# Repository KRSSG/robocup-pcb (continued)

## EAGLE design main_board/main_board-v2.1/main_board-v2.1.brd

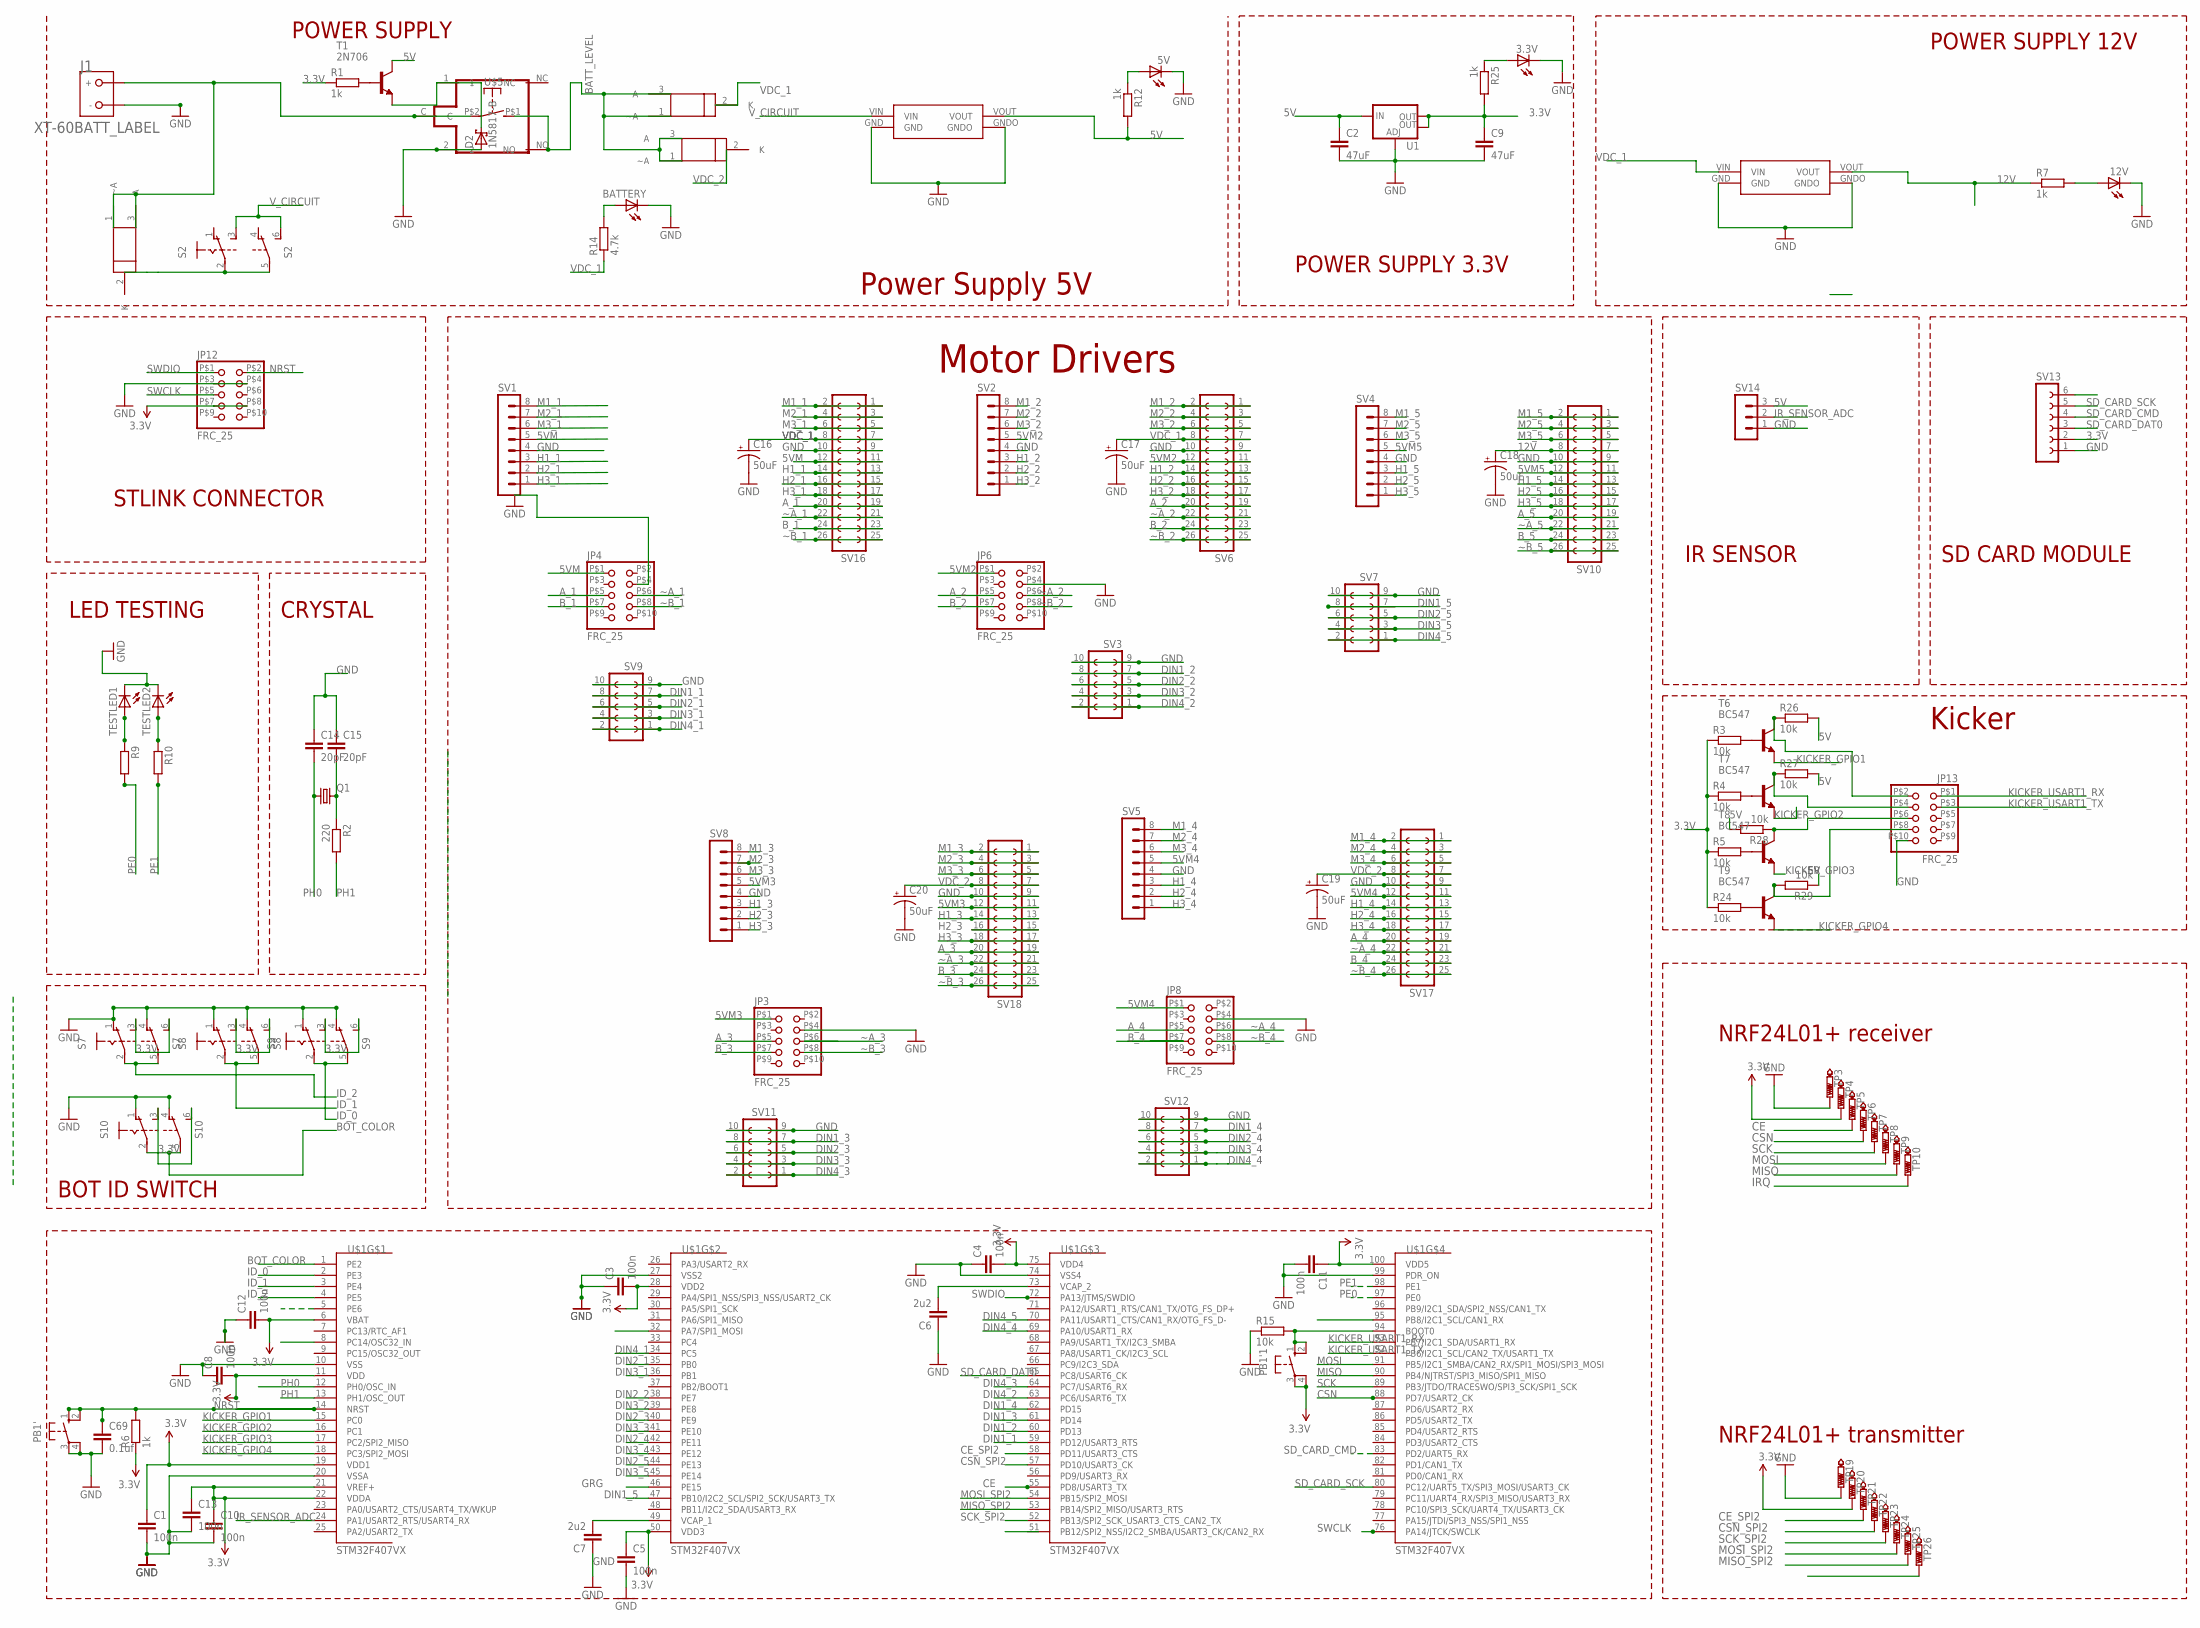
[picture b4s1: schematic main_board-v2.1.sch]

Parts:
3.3V, 5V, 12V: LEDCHIPLED_1206; CHIPLED_1206
BATTERY: LEDCHIPLED_1206; CHIPLED_1206
C1, C3, C4, C5, C8, C10, C11, C12, C13: 100n; C1206
C2, C9: 47uF; C1206
C6, C7: 2u2; C1206
C14, C15: 20pF; C1206
C16, C17, C18, C19, C20: 50uF; E3,5-8
C69: 0.1uf; C1206
D2: 1N5817-B; DO41-7.6
J1: XT-60BATT_LABEL; XT-60
JP3, JP4, JP6, JP8, JP12, JP13: FRC_25; FRC2*5
PB1', PB1'1: 10-XX; B3F-10XX
Q1: CRYSTALHC49U-V; HC49U-V
R1, R6, R7, R12, R25: 1k; R1206
R2: 220; R1206
R3, R4, R5, R15, R24, R26, R27, R28, R29: 10k; R1206
R9, R10: R-EU_R1206; R1206
R14: 4.7k; R1206
S2, S7, S8, S9, S10: A68-A31
SV1, SV2, SV4, SV5, SV8: MA08-1
SV3, SV7, SV9, SV11, SV12: FE05-2
SV6, SV10, SV16, SV17, SV18: FE13-2
SV13: FE06-1; FE06
SV14: MA03-1
T1: 2N706; TO18
T6, T7, T8, T9: BC547; TO92
TESTLED1, TESTLED2: LEDCHIPLED_1206; CHIPLED_1206
TP3, TP4, TP5, TP6, TP7, TP8, TP9, TP10, TP19, TP20, TP21, TP22, TP23, TP24, TP25, TP26: PTR1PAD1-13; P1-13
U1: V_REG_LM1117SOT223; SOT223
U2, U3, U4: LP38690DT-3.3; TO228P1042X238-3N
U$1: STM32F407VX; LQFP100
U$2: REL
U$3, U$4: BUCK
U$5: SWITCH_DA10; DA10

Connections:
3.3V: C1.1, C3.2, C4.2, C5.1, C8.2, C9.1, C10.1, C11.1, C12.2, C13.1, JP12.P$7 (7), JP12.P$8 (8), PB1'1.3, PB1'1.4 (P1), R3.1, R4.1, R5.1, R6.1, R24.1, R25.2, S7.3 (S), S7.6 (S), S8.3 (S), S8.6 (S), S9.3 (S), S9.6 (S), S10.3 (S), S10.6 (S), SV13.2, TP4.TP, TP20.TP, U1.2 (OUT), U1.4 (OUT), U$1.6 (VBAT), U$1.11 (VDD), U$1.19 (VDD1), U$1.21 (VREF+), U$1.22 (VDDA), U$1.28 (VDD2), U$1.50 (VDD3), U$1.75 (VDD4), U$1.100 (VDD5)
5V: C2.1, R12.2, R26.2, R27.2, R28.2, R29.1, SV14.3, T1.3 (C), U1.3 (IN), U$3.VOUT
5VM: JP4.P$1 (1), SV1.5, SV16.11, SV16.12
5VM2: JP6.P$1 (1), SV2.5, SV6.11, SV6.12
5VM3: JP3.P$1 (1), SV8.5, SV18.11, SV18.12
5VM4: JP8.P$1 (1), SV5.5, SV17.11, SV17.12
5VM5: SV4.5, SV10.11, SV10.12
12V: C18.+, R7.1, SV10.7, SV10.8, U$4.VOUT
A_1: JP4.P$5 (5), SV16.19, SV16.20
A_2: JP6.P$5 (5), SV6.19, SV6.20
A_3: JP3.P$5 (5), SV18.19, SV18.20
A_4: JP8.P$5 (5), SV17.19, SV17.20
A_5: SV10.19, SV10.20
BATT_LEVEL: U2.1 (~A), U2.3 (A), U4.1 (~A), U4.3 (A), U$2.NO, U$5.P$1 (S)
BOT_COLOR: S10.2, S10.5, U$1.1 (PE2)
B_1: JP4.P$7 (7), SV16.23, SV16.24
B_2: JP6.P$7 (7), SV6.23, SV6.24
B_3: JP3.P$7 (7), SV18.23, SV18.24
B_4: JP8.P$7 (7), SV17.23, SV17.24
B_5: SV10.23, SV10.24
CE: TP5.TP, U$1.55 (PD8/USART3_TX)
CE_SPI2: TP21.TP, U$1.58 (PD11/USART3_CTS)
CSN: TP6.TP, U$1.88 (PD7/USART2_CK)
CSN_SPI2: TP22.TP, U$1.57 (PD10/USART3_CK)
DIN1_1: SV9.7, SV9.8, U$1.59 (PD12/USART3_RTS)
DIN1_2: SV3.7, SV3.8, U$1.60 (PD13)
DIN1_3: SV11.7, SV11.8, U$1.61 (PD14)
DIN1_4: SV12.7, SV12.8, U$1.62 (PD15)
DIN1_5: SV7.7, SV7.8, U$1.47 (PB10/I2C2_SCL/SPI2_SCK/USART3_TX)
DIN2_1: SV9.5, SV9.6, U$1.35 (PB0)
DIN2_2: SV3.5, SV3.6, U$1.38 (PE7)
DIN2_3: SV11.5, SV11.6, U$1.40 (PE9)
DIN2_4: SV12.5, SV12.6, U$1.42 (PE11)
DIN2_5: SV7.5, SV7.6, U$1.44 (PE13)
DIN3_1: SV9.3, SV9.4, U$1.36 (PB1)
DIN3_2: SV3.3, SV3.4, U$1.39 (PE8)
DIN3_3: SV11.3, SV11.4, U$1.41 (PE10)
DIN3_4: SV12.3, SV12.4, U$1.43 (PE12)
DIN3_5: SV7.3, SV7.4, U$1.45 (PE14)
DIN4_1: SV9.1, SV9.2, U$1.34 (PC5)
DIN4_2: SV3.1, SV3.2, U$1.63 (PC6/USART6_TX)
DIN4_3: SV11.1, SV11.2, U$1.64 (PC7/USART6_RX)
DIN4_4: SV12.1, SV12.2, U$1.69 (PA10/USART1_RX)
DIN4_5: SV7.1, SV7.2, U$1.70 (PA11/USART1_CTS/CAN1_RX/OTG_FS_D-)
GND: 3.3V.C, 5V.C, 12V.C, BATTERY.C, C1.2, C2.2, C3.1, C4.1, C5.2, C6.1, C7.1, C8.1, C9.2, C10.2, C11.2, C12.1, C13.2, C14.1, C15.1, C16.-, C17.-, C18.-, C19.-, C20.-, C69.2, D2.A, J1.GND (-), JP3.P$4 (4), JP4.P$4 (4), JP6.P$4 (4), JP8.P$4 (4), JP12.P$3 (3), JP12.P$4 (4), JP13.P$10 (10), PB1'.3, PB1'.4 (P1), R15.1, S7.1 (O), S7.4 (O), S8.1 (O), S8.4 (O), S9.1 (O), S9.4 (O), S10.1 (O), S10.4 (O), SV1.4, SV2.4, SV3.9, SV3.10, SV4.4, SV5.4, SV6.9, SV6.10, SV7.9, SV7.10, SV8.4, SV9.9, SV9.10, SV10.9, SV10.10, SV11.9, SV11.10, SV12.9, SV12.10, SV13.1, SV14.1, SV16.9, SV16.10, SV17.9, SV17.10, SV18.9, SV18.10, TESTLED1.C, TESTLED2.C, TP3.TP, TP19.TP, U1.1 (ADJ), U$1.10 (VSS), U$1.20 (VSSA), U$1.27 (VSS2), U$1.74 (VSS4), U$1.99 (PDR_ON), U$2.2, U$3.GND, U$3.GNDO, U$4.GND, U$4.GNDO
GRG: U$1.46 (PE15)
H1_1: SV1.3, SV16.13, SV16.14
H1_2: SV2.3, SV6.13, SV6.14
H1_3: SV8.3, SV18.13, SV18.14
H1_4: SV5.3, SV17.13, SV17.14
H1_5: SV4.3, SV10.13, SV10.14
H2_1: SV1.2, SV16.15, SV16.16
H2_2: SV2.2, SV6.15, SV6.16
H2_3: SV8.2, SV18.15, SV18.16
H2_4: SV5.2, SV17.15, SV17.16
H2_5: SV4.2, SV10.15, SV10.16
H3_1: SV1.1, SV16.17, SV16.18
H3_2: SV2.1, SV6.17, SV6.18
H3_3: SV8.1, SV18.17, SV18.18
H3_4: SV5.1, SV17.17, SV17.18
H3_5: SV4.1, SV10.17, SV10.18
ID_0: S9.2, S9.5, U$1.2 (PE3)
ID_1: S8.2, S8.5, U$1.3 (PE4)
ID_2: S7.2, S7.5, U$1.4 (PE5)
IRQ: TP10.TP
IRQ_SPI2: U$1.8 (PC14/OSC32_IN)
IR_SENSOR_ADC: SV14.2, U$1.24 (PA1/USART2_RTS/USART4_RX)
KICKER_GPIO1: T6.1 (E), U$1.15 (PC0)
KICKER_GPIO2: T7.1 (E), U$1.16 (PC1)
KICKER_GPIO3: T8.1 (E), U$1.17 (PC2/SPI2_MISO)
KICKER_GPIO4: T9.1 (E), U$1.18 (PC3/SPI2_MOSI)
KICKER_USART1_RX: JP13.P$1 (1), U$1.93 (PB7/I2C1_SDA/USART1_RX)
KICKER_USART1_TX: JP13.P$3 (3), U$1.92 (PB6/I2C1_SCL/CAN2_TX/USART1_TX)
M1_1: SV1.8, SV16.1, SV16.2
M1_2: SV2.8, SV6.1, SV6.2
M1_3: SV8.8, SV18.1, SV18.2
M1_4: SV5.8, SV17.1, SV17.2
M1_5: SV4.8, SV10.1, SV10.2
M2_1: SV1.7, SV16.3, SV16.4
M2_2: SV2.7, SV6.3, SV6.4
M2_3: SV8.7, SV18.3, SV18.4
M2_4: SV5.7, SV17.3, SV17.4
M2_5: SV4.7, SV10.3, SV10.4
M3_1: SV1.6, SV16.5, SV16.6
M3_2: SV2.6, SV6.5, SV6.6
M3_3: SV8.6, SV18.5, SV18.6
M3_4: SV5.6, SV17.5, SV17.6
M3_5: SV4.6, SV10.5, SV10.6
MISO: TP9.TP, U$1.90 (PB4/NJTRST/SPI3_MISO/SPI1_MISO)
MISO_SPI2: TP25.TP, U$1.53 (PB14/SPI2_MISO/USART3_RTS)
MOSI: TP8.TP, U$1.91 (PB5/I2C1_SMBA/CAN2_RX/SPI1_MOSI/SPI3_MO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)
MOSI_SPI2: TP24.TP, U$1.54 (PB15/SPI2_MOSI)
unnamed: R10.1, TESTLED2.A
unnamed: C7.2, U$1.49 (VCAP_1)
unnamed: C6.2, U$1.73 (VCAP_2)
unnamed: PB1'1.1 (S), PB1'1.2 (S1), R15.2, U$1.94 (BOOT0)
unnamed: R9.1, TESTLED1.A
unnamed: C15.2, Q1.2, R2.1
unnamed: 5V.A, R12.1
unnamed: J1.BATT (+), U3.1 (~A), U3.3 (A), U$2.C, U$5.P$2
unnamed: 12V.A, R7.2
unnamed: BATTERY.A, R14.2
unnamed: 3.3V.A, R25.1
unnamed: R1.2, T1.2 (B)
unnamed: D2.C, T1.1 (E), U$2.1
unnamed: S2.2, S2.5, U3.2 (K)
unnamed: R5.2, T8.2 (B)
unnamed: R3.2, T6.2 (B)
unnamed: R4.2, T7.2 (B)
unnamed: R24.2, T9.2 (B)
unnamed: JP13.P$2 (2), R26.1, T6.3 (C)
unnamed: JP13.P$4 (4), R27.1, T7.3 (C)
unnamed: JP13.P$6 (6), R28.1, T8.3 (C)
unnamed: JP13.P$8 (8), R29.2, T9.3 (C)
NRST: C69.1, JP12.P$2 (2), PB1'.1 (S), PB1'.2 (S1), R6.2, U$1.14 (NRST)
PE0: R9.2, U$1.97 (PE0)
PE1: R10.2, U$1.98 (PE1)
PH0: C14.2, Q1.1, U$1.12 (PH0/OSC_IN)
PH1: R2.2, U$1.13 (PH1/OSC_OUT)
SCK: TP7.TP, U$1.89 (PB3/JTDO/TRACESWO/SPI3_SCK/SPI1_SCK)
SCK_SPI2: TP23.TP, U$1.52 (PB13/SPI2_SCK_USART3_CTS_CAN2_TX)
SD_CARD_CMD: SV13.4, U$1.83 (PD2/UART5_RX)
SD_CARD_DAT0: SV13.3, U$1.65 (PC8/USART6_CK)
SD_CARD_SCK: SV13.5, U$1.80 (PC12/UART5_TX/SPI3_MOSI/USART3_CK)
SWCLK: JP12.P$5 (5), U$1.76 (PA14/JTCK/SWCLK)
SWDIO: JP12.P$1 (1), U$1.72 (PA13/JTMS/SWDIO)
VDC_1: C16.+, C17.+, R14.1, SV6.7, SV6.8, SV16.7, SV16.8, U4.2 (K), U$4.VIN
VDC_2: C19.+, C20.+, SV17.7, SV17.8, SV18.7, SV18.8, U2.2 (K)
V_CIRCUIT: S2.3 (S), S2.6 (S), U$3.VIN
~A_1: JP4.P$6 (6), SV16.21, SV16.22
~A_2: JP6.P$6 (6), SV6.21, SV6.22
~A_3: JP3.P$6 (6), SV18.21, SV18.22
~A_4: JP8.P$6 (6), SV17.21, SV17.22
~A_5: SV10.21, SV10.22
~B_1: JP4.P$8 (8), SV16.25, SV16.26
~B_2: JP6.P$8 (8), SV6.25, SV6.26
~B_3: JP3.P$8 (8), SV18.25, SV18.26
~B_4: JP8.P$8 (8), SV17.25, SV17.26
~B_5: SV10.25, SV10.26

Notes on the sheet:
NRF24L01+ receiver
STLINK CONNECTOR
LED TESTING
Motor Drivers
POWER SUPPLY 12V
POWER SUPPLY 3.3V
Kicker
NRF24L01+ transmitter
POWER SUPPLY
Power Supply 5V
BOT ID SWITCH
CRYSTAL
SD CARD MODULE
IR SENSOR

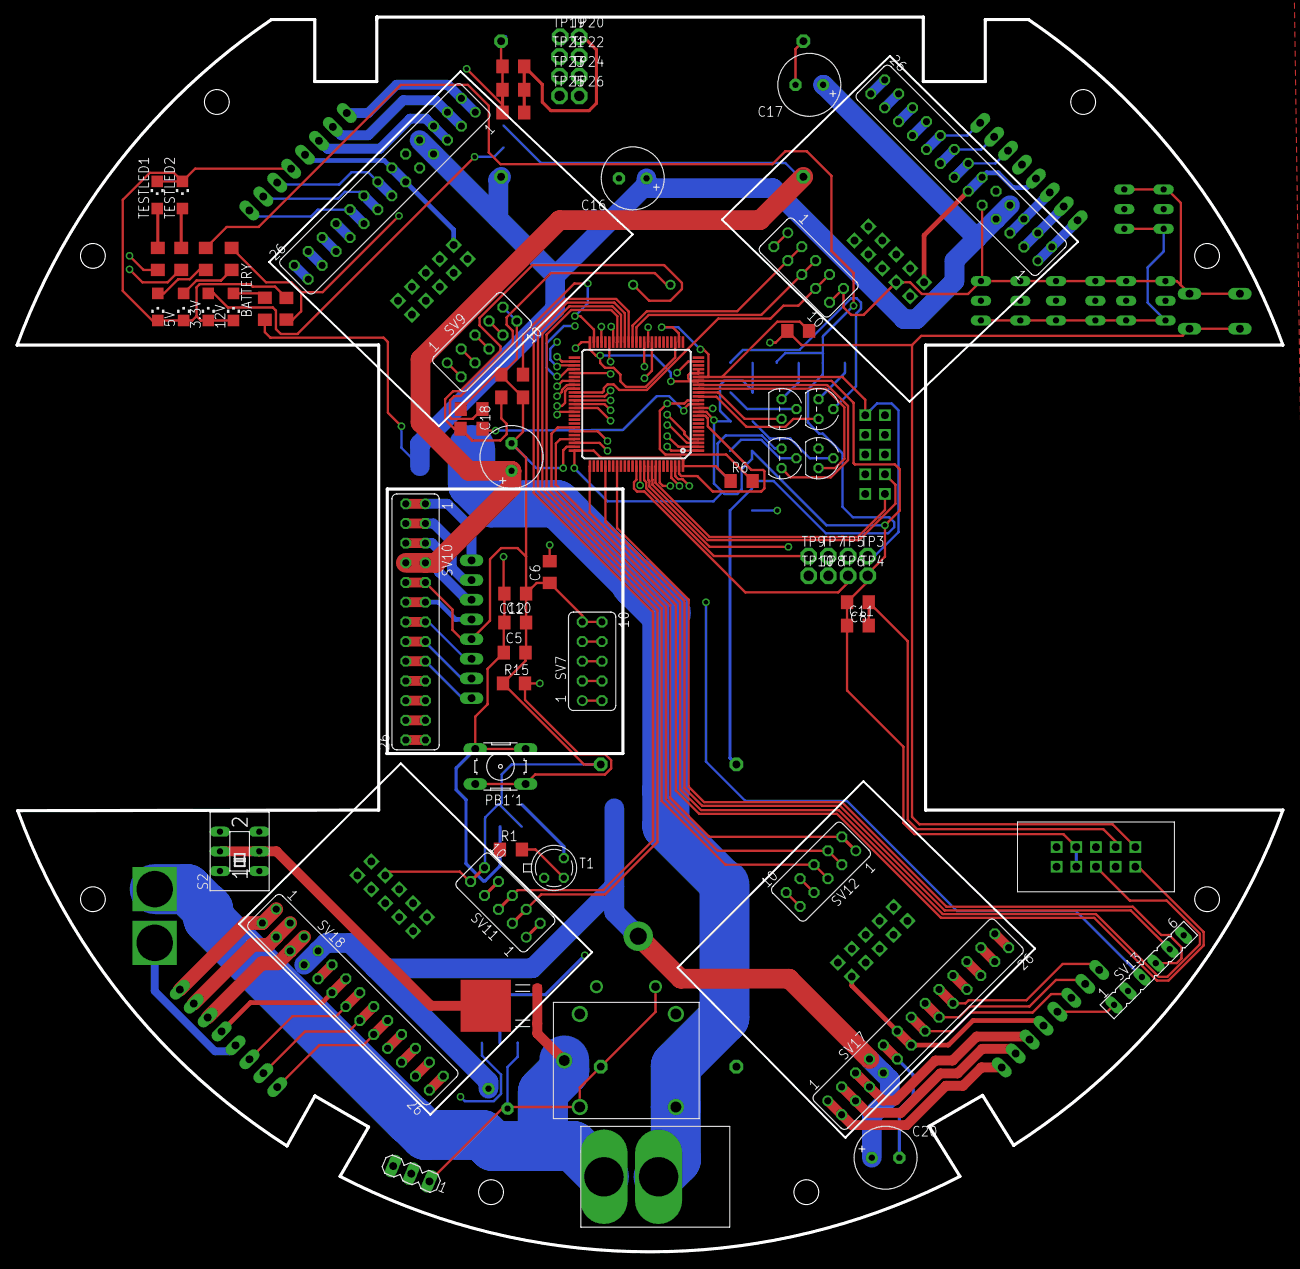
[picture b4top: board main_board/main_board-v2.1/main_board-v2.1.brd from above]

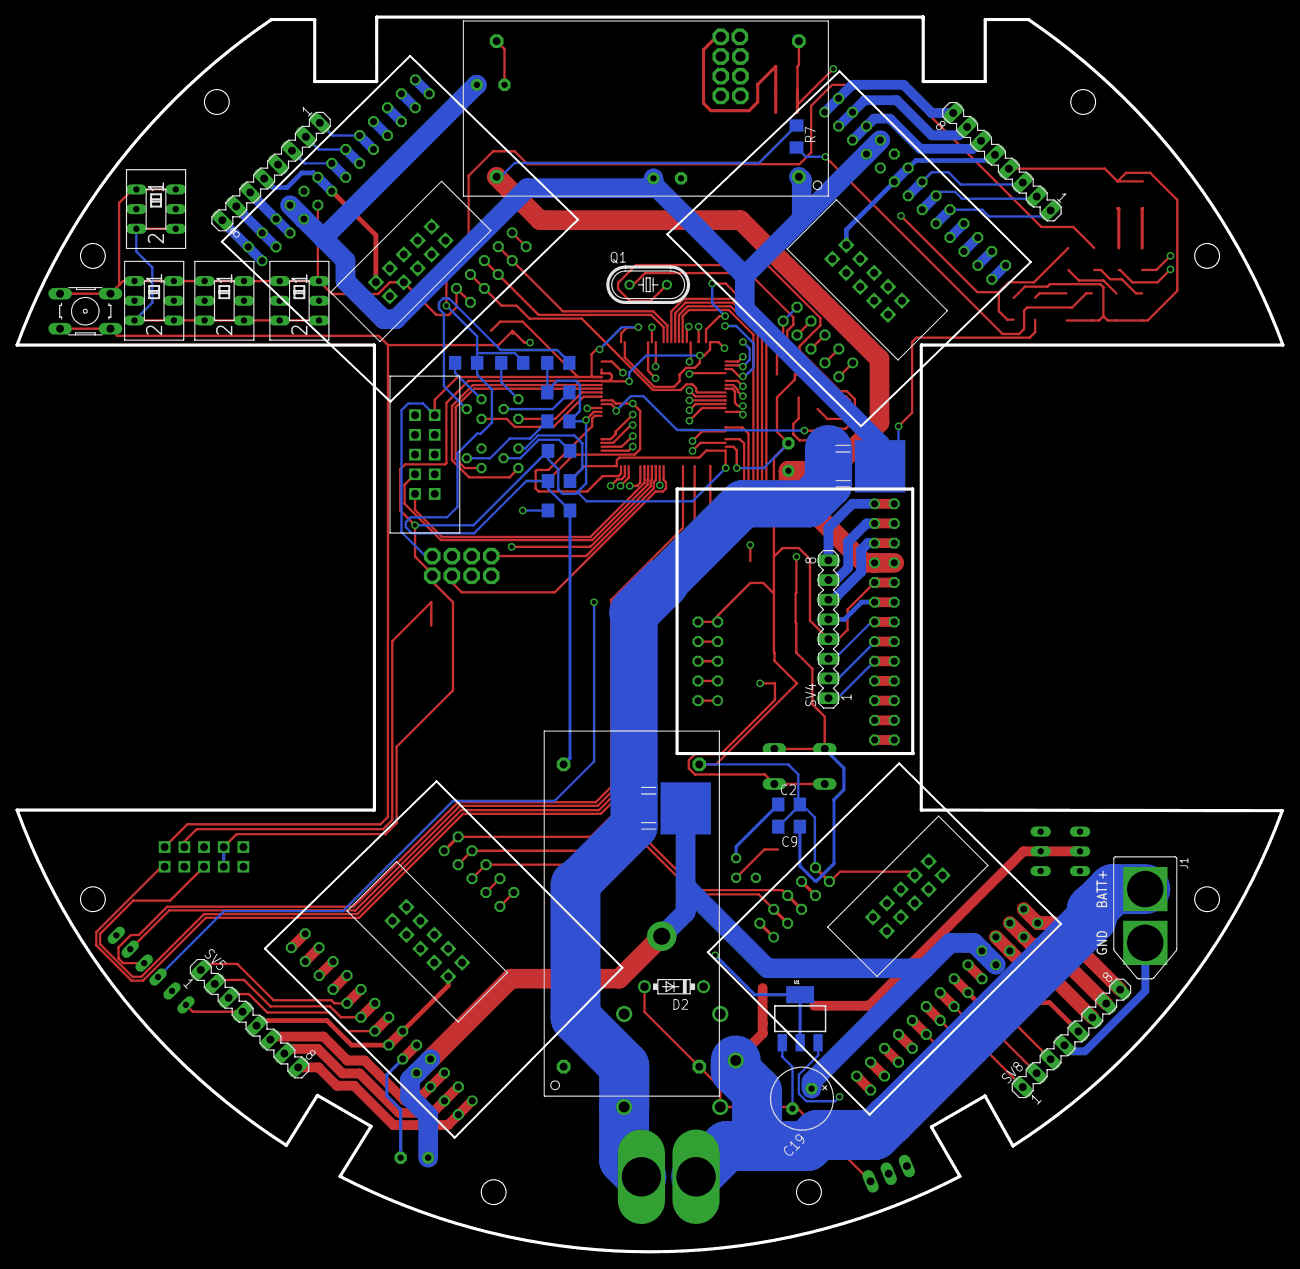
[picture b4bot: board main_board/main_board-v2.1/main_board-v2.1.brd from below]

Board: 4 copper layers, 163.3 x 159.3 mm, 108 parts (35 on the bottom side), 136 nets.

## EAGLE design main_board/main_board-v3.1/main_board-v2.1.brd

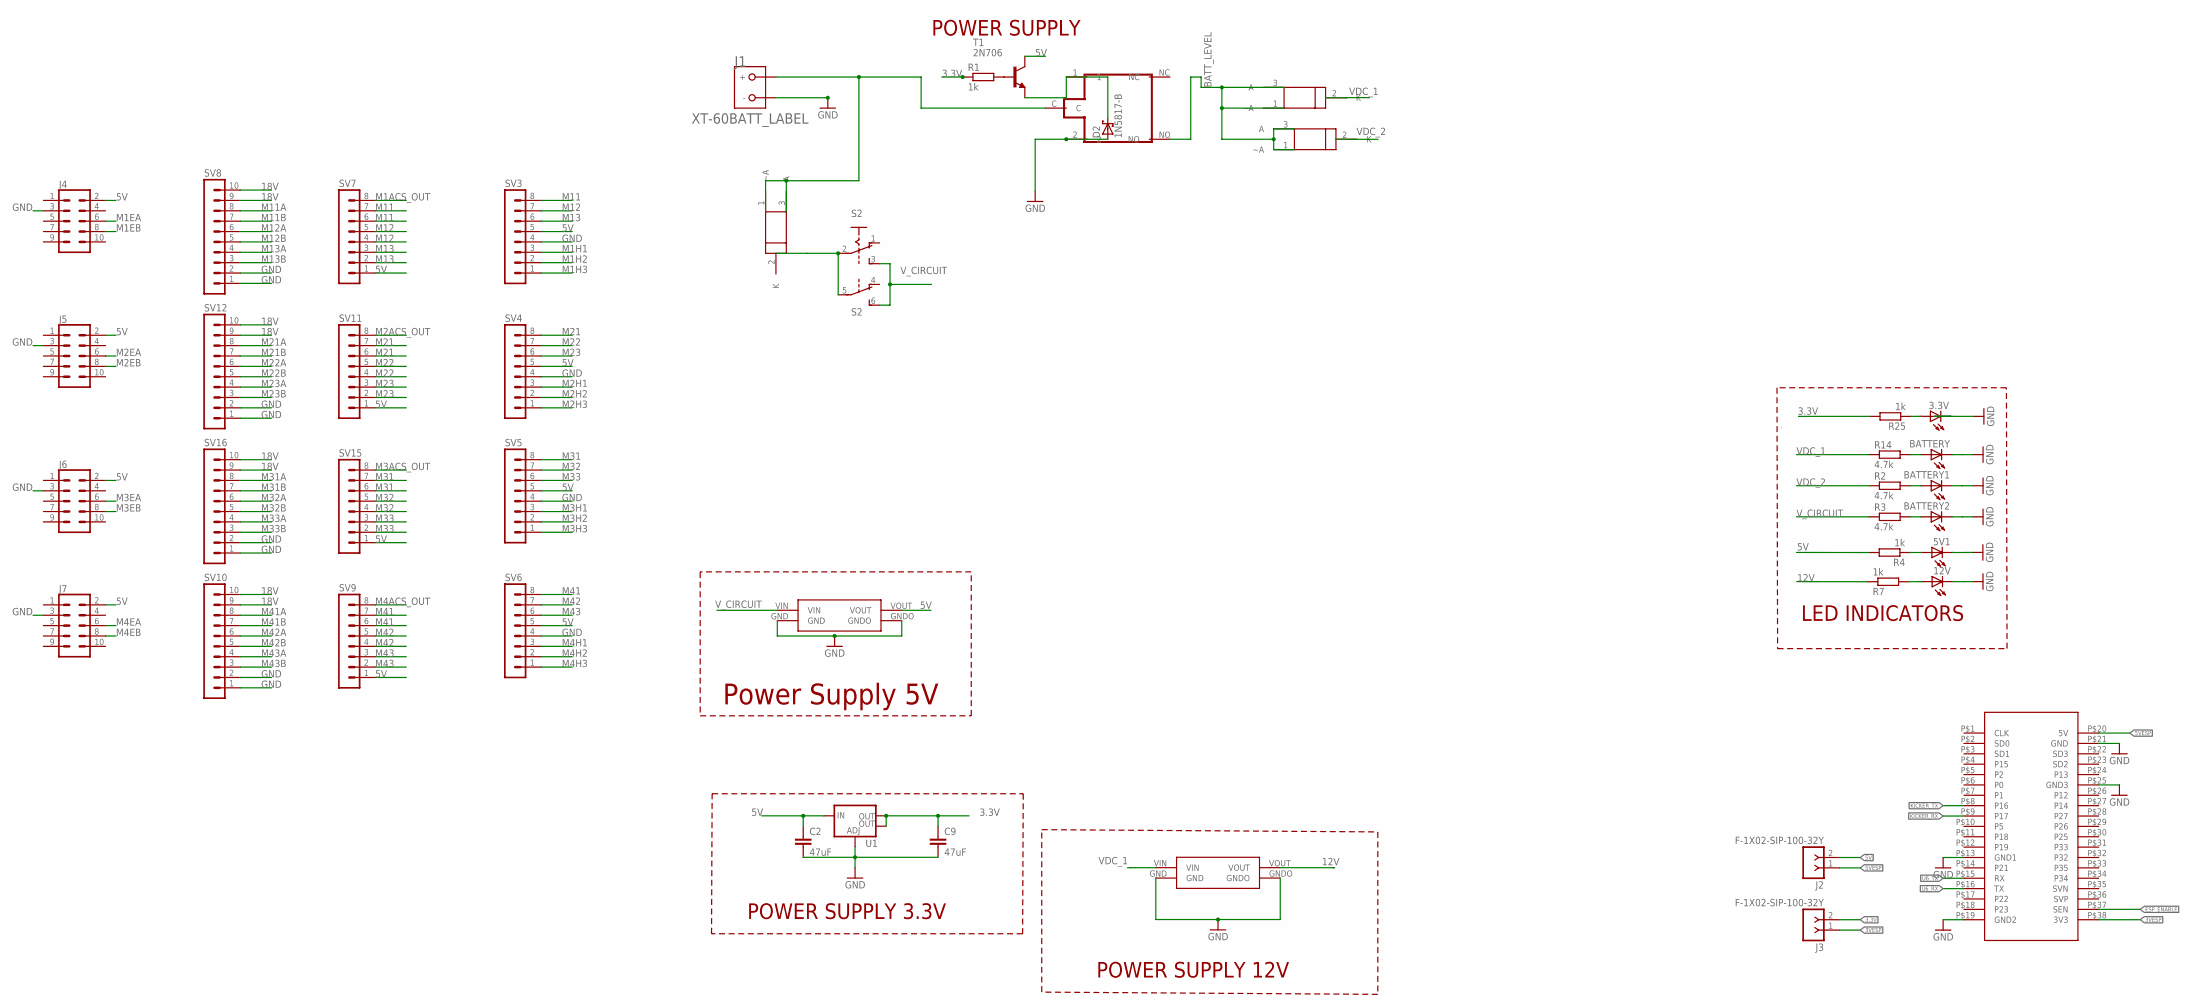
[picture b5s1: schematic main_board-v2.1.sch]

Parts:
3.3V, 5V1, 12V: LEDCHIPLED_0805; CHIPLED_0805
BATTERY, BATTERY1, BATTERY2: LEDCHIPLED_0805; CHIPLED_0805
C2, C9: 47uF; C1206
D2: 1N5817-B; DO41-7.6
J1: XT-60BATT_LABEL; XT-60
J2, J3: F-1X02-SIP-100-32Y; SIP-100-02-32Y
J4, J5, J6, J7: CONN_05X2SHD_LOCK; 2X5-SHROUDED_LOCK
R1, R4, R7, R25: 1k; R1206
R2, R3, R14: 4.7k; R1206
S2: A68-A31
SV3, SV4, SV5, SV6, SV7, SV9, SV11, SV15: MA08-1
SV8, SV10, SV12, SV16: MA10-1
T1: 2N706; TO18
U1: V_REG_LM1117SOT223; SOT223
U2, U3, U4: LP38690DT-3.3; TO228P1042X238-3N
U$2: REL
U$3, U$4: BUCK
U$6: NODEMCU32S; NODEMCU32

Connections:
3.3V: C9.1, J3.2, R1.1, R25.2, U1.2 (OUT), U1.4 (OUT)
3VESP: J3.1, U$6.P$38 (3V3)
5V: C2.1, J2.2, J4.2, J5.2, J6.2, J7.2, R4.2, SV3.5, SV4.5, SV5.5, SV6.5, SV7.1, SV9.1, SV11.1, SV15.1, T1.3 (C), U1.3 (IN), U$3.VOUT
5VESP: J2.1, U$6.P$20 (5V)
12V: R7.1, U$4.VOUT
18V: SV8.9, SV8.10, SV10.9, SV10.10, SV12.9, SV12.10, SV16.9, SV16.10
BATT_LEVEL: U2.1 (~A), U2.3 (A), U4.1 (~A), U4.3 (A), U$2.NO
ESP_ENABLE: U$6.P$37 (SEN)
GND: 3.3V.C, 5V1.C, 12V.C, BATTERY.C, BATTERY1.C, BATTERY2.C, C2.2, C9.2, D2.A, J1.GND (-), J4.3, J5.3, J6.3, J7.3, SV3.4, SV4.4, SV5.4, SV6.4, SV8.1, SV8.2, SV10.1, SV10.2, SV12.1, SV12.2, SV16.1, SV16.2, U1.1 (ADJ), U$2.2, U$3.GND, U$3.GNDO, U$4.GND, U$4.GNDO, U$6.P$13 (GND1), U$6.P$19 (GND2), U$6.P$21 (GND), U$6.P$25 (GND3)
INPUT: J1.BATT (+), U3.1 (~A), U3.3 (A), U$2.C
KICKER_RX: U$6.P$9 (P17)
KICKER_TX: U$6.P$8 (P16)
M1ACS_OUT: SV7.8
M1EA: J4.6
M1EB: J4.8
M1H1: SV3.3
M1H2: SV3.2
M1H3: SV3.1
M2ACS_OUT: SV11.8
M2EA: J5.6
M2EB: J5.8
M2H1: SV4.3
M2H2: SV4.2
M2H3: SV4.1
M3ACS_OUT: SV15.8
M3EA: J6.6
M3EB: J6.8
M3H1: SV5.3
M3H2: SV5.2
M3H3: SV5.1
M4ACS_OUT: SV9.8
M4EA: J7.6
M4EB: J7.8
M4H1: SV6.3
M4H2: SV6.2
M4H3: SV6.1
M11: SV3.8, SV7.6, SV7.7
M11A: SV8.8
M11B: SV8.7
M12: SV3.7, SV7.4, SV7.5
M12A: SV8.6
M12B: SV8.5
M13: SV3.6, SV7.2, SV7.3
M13A: SV8.4
M13B: SV8.3
M21: SV4.8, SV11.6, SV11.7
M21A: SV12.8
M21B: SV12.7
M22: SV4.7, SV11.4, SV11.5
M22A: SV12.6
M22B: SV12.5
M23: SV4.6, SV11.2, SV11.3
M23A: SV12.4
M23B: SV12.3
M31: SV5.8, SV15.6, SV15.7
M31A: SV16.8
M31B: SV16.7
M32: SV5.7, SV15.4, SV15.5
M32A: SV16.6
M32B: SV16.5
M33: SV5.6, SV15.2, SV15.3
M33A: SV16.4
M33B: SV16.3
M41: SV6.8, SV9.6, SV9.7
M41A: SV10.8
M41B: SV10.7
M42: SV6.7, SV9.4, SV9.5
M42A: SV10.6
M42B: SV10.5
M43: SV6.6, SV9.2, SV9.3
M43A: SV10.4
M43B: SV10.3
unnamed: BATTERY1.A, R2.2
unnamed: BATTERY2.A, R3.2
unnamed: 5V1.A, R4.1
unnamed: 12V.A, R7.2
unnamed: BATTERY.A, R14.2
unnamed: 3.3V.A, R25.1
unnamed: R1.2, T1.2 (B)
unnamed: D2.C, T1.1 (E), U$2.1
unnamed: S2.2, S2.5, U3.2 (K)
U6_RX: U$6.P$16 (TX)
U6_TX: U$6.P$15 (RX)
VDC_1: R14.1, U4.2 (K), U$4.VIN
VDC_2: R2.1, U2.2 (K)
V_CIRCUIT: R3.1, S2.3 (S), S2.6 (S), U$3.VIN

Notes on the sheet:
POWER SUPPLY
Power Supply 5V
POWER SUPPLY 12V
POWER SUPPLY 3.3V
LED INDICATORS

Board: 4 copper layers, 45 parts (0 on the bottom side), 33 nets, no tracks yet.

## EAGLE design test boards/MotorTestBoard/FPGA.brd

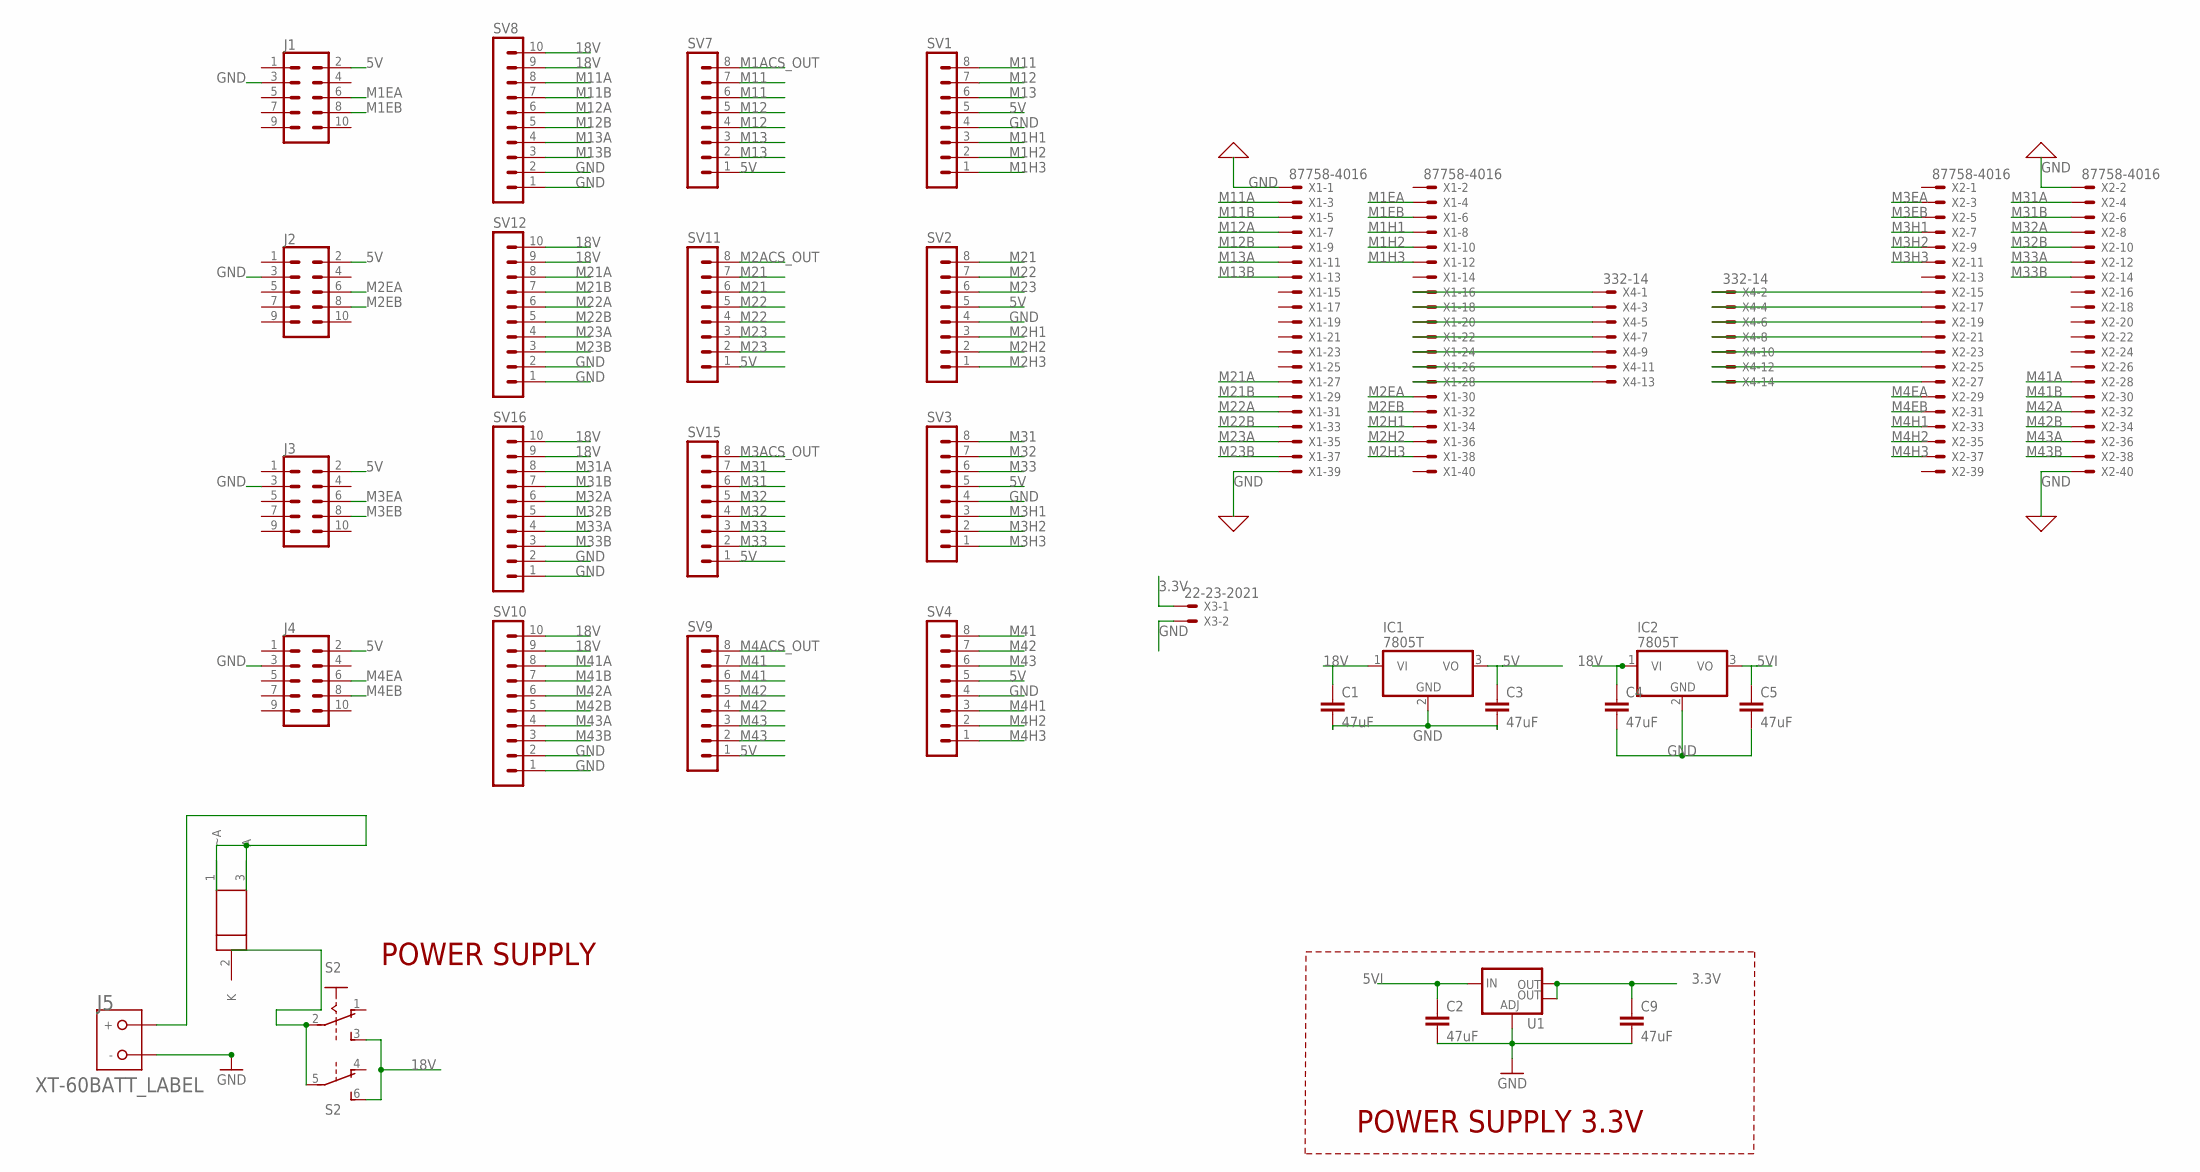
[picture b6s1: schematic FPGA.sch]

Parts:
C1, C2, C3, C4, C5, C9: 47uF; C1206
IC1, IC2: 7805T; TO220H
J1, J2, J3, J4: CONN_05X2SHD_LOCK; 2X5-SHROUDED_LOCK
J5: XT-60BATT_LABEL; XT-60
S2: A68-A31
SV1, SV2, SV3, SV4, SV7, SV9, SV11, SV15: MA08-1
SV8, SV10, SV12, SV16: MA10-1
U1: V_REG_LM1117SOT223; SOT223
U3: LP38690DT-3.3; TO228P1042X238-3N
X1, X2: 87758-4016
X3: 22-23-2021
X4: 332-14

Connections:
3.3V: C9.1, U1.2 (OUT), U1.4 (OUT), X3.1
5V: C3.1, IC1.3 (VO), J1.2, J2.2, J3.2, J4.2, SV1.5, SV2.5, SV3.5, SV4.5, SV7.1, SV9.1, SV11.1, SV15.1
5VI: C2.1, C5.1, IC2.3 (VO), U1.3 (IN)
18V: C1.1, C4.1, IC1.1 (VI), IC2.1 (VI), S2.3 (S), S2.6 (S), SV8.9, SV8.10, SV10.9, SV10.10, SV12.9, SV12.10, SV16.9, SV16.10
GND: C1.2, C2.2, C3.2, C4.2, C5.2, C9.2, IC1.2 (GND), IC2.2 (GND), J1.3, J2.3, J3.3, J4.3, J5.GND (-), SV1.4, SV2.4, SV3.4, SV4.4, SV8.1, SV8.2, SV10.1, SV10.2, SV12.1, SV12.2, SV16.1, SV16.2, U1.1 (ADJ), X1.1, X1.39, X2.2, X2.40, X3.2
INPUT: J5.BATT (+), U3.1 (~A), U3.3 (A)
M1ACS_OUT: SV7.8
M1EA: J1.6, X1.4
M1EB: J1.8, X1.6
M1H1: SV1.3, X1.8
M1H2: SV1.2, X1.10
M1H3: SV1.1, X1.12
M2ACS_OUT: SV11.8
M2EA: J2.6, X1.30
M2EB: J2.8, X1.32
M2H1: SV2.3, X1.34
M2H2: SV2.2, X1.36
M2H3: SV2.1, X1.38
M3ACS_OUT: SV15.8
M3EA: J3.6, X2.3
M3EB: J3.8, X2.5
M3H1: SV3.3, X2.7
M3H2: SV3.2, X2.9
M3H3: SV3.1, X2.11
M4ACS_OUT: SV9.8
M4EA: J4.6, X2.29
M4EB: J4.8, X2.31
M4H1: SV4.3, X2.33
M4H2: SV4.2, X2.35
M4H3: SV4.1, X2.37
M11: SV1.8, SV7.6, SV7.7
M11A: SV8.8, X1.3
M11B: SV8.7, X1.5
M12: SV1.7, SV7.4, SV7.5
M12A: SV8.6, X1.7
M12B: SV8.5, X1.9
M13: SV1.6, SV7.2, SV7.3
M13A: SV8.4, X1.11
M13B: SV8.3, X1.13
M21: SV2.8, SV11.6, SV11.7
M21A: SV12.8, X1.27
M21B: SV12.7, X1.29
M22: SV2.7, SV11.4, SV11.5
M22A: SV12.6, X1.31
M22B: SV12.5, X1.33
M23: SV2.6, SV11.2, SV11.3
M23A: SV12.4, X1.35
M23B: SV12.3, X1.37
M31: SV3.8, SV15.6, SV15.7
M31A: SV16.8, X2.4
M31B: SV16.7, X2.6
M32: SV3.7, SV15.4, SV15.5
M32A: SV16.6, X2.8
M32B: SV16.5, X2.10
M33: SV3.6, SV15.2, SV15.3
M33A: SV16.4, X2.12
M33B: SV16.3, X2.14
M41: SV4.8, SV9.6, SV9.7
M41A: SV10.8, X2.28
M41B: SV10.7, X2.30
M42: SV4.7, SV9.4, SV9.5
M42A: SV10.6, X2.32
M42B: SV10.5, X2.34
M43: SV4.6, SV9.2, SV9.3
M43A: SV10.4, X2.36
M43B: SV10.3, X2.38
unnamed: X1.16, X4.1
unnamed: X1.18, X4.3
unnamed: X1.20, X4.5
unnamed: X1.22, X4.7
unnamed: X1.24, X4.9
unnamed: X1.26, X4.11
unnamed: X1.28, X4.13
unnamed: X2.27, X4.14
unnamed: X2.25, X4.12
unnamed: X2.23, X4.10
unnamed: X2.21, X4.8
unnamed: X2.19, X4.6
unnamed: X2.17, X4.4
unnamed: X2.15, X4.2
unnamed: S2.2, S2.5, U3.2 (K)

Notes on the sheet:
POWER SUPPLY 3.3V
POWER SUPPLY

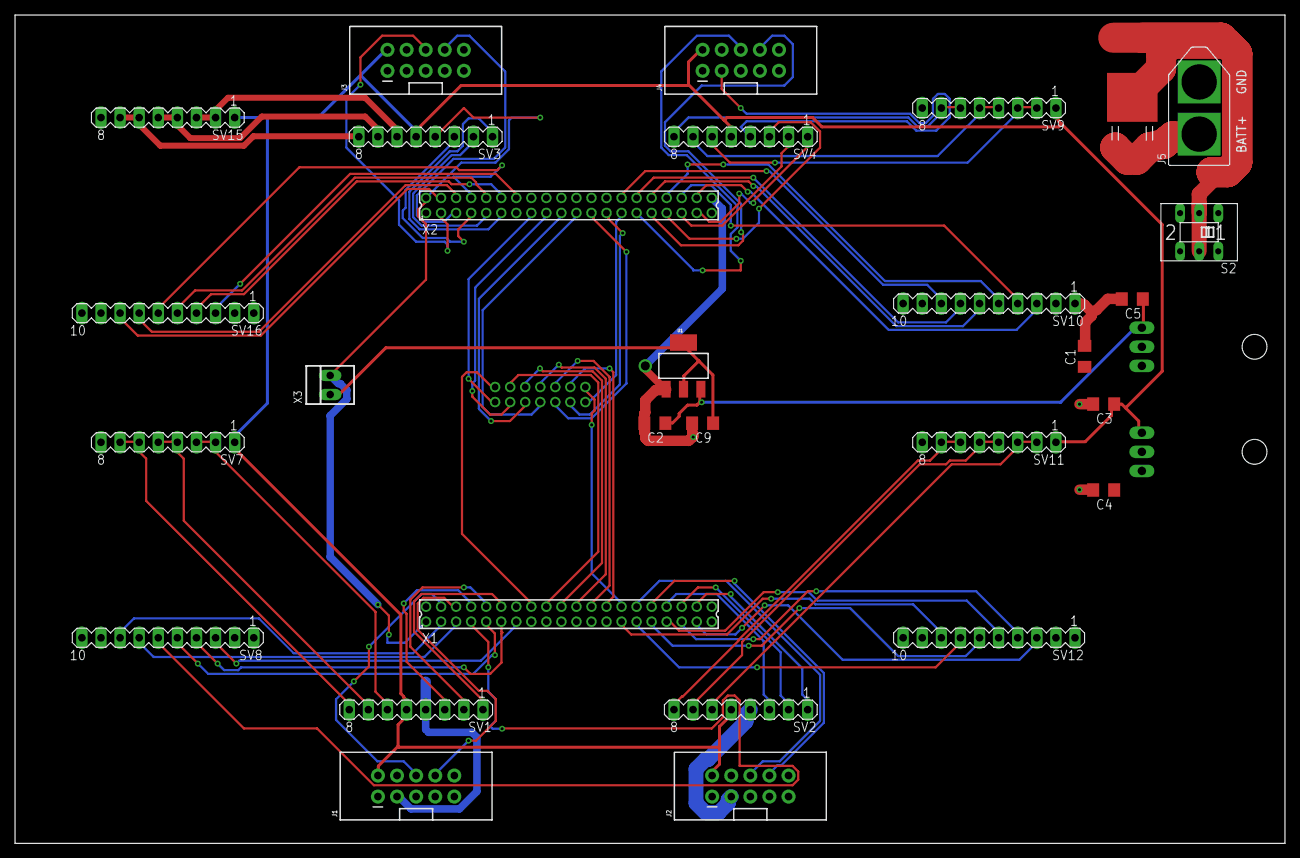
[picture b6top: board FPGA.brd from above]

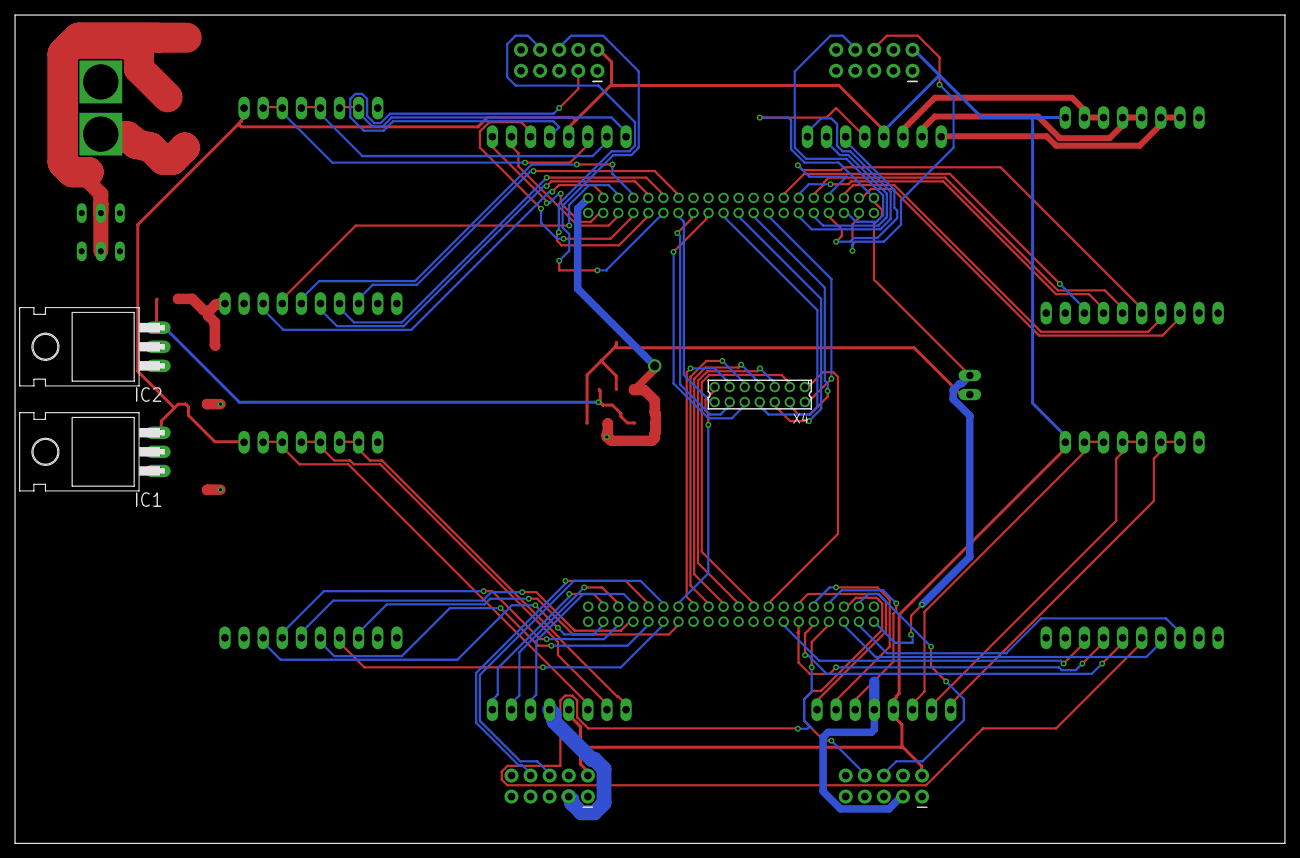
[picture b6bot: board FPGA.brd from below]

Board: 2 copper layers, 168.9 x 110.2 mm, 32 parts (3 on the bottom side), 77 nets.

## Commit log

2018-05-13 kicker-v1
2018-05-13 kicker-v2.1
2018-05-13 kicker-v2.2
2018-05-13 uc2950-v1
2018-05-13 main_board-v2.1
2018-05-13 main_board-v1
2018-05-13 main_board-v2.2
2018-05-18 Completed Circuit
2018-05-20 added 12v, fixed previous issues
2018-05-20 header pin placement changed
2018-05-21 "Kicker"
2018-07-12 Completed
2018-07-12 Modified
2018-07-12 temp files
2018-07-12 IR4427 v1
2018-08-02 A3930
2018-08-02 IR4427
2018-08-02 Clean
2018-08-02 Kicker proto
2018-08-02 Final Data
2018-08-06 Enclosed
2018-08-07 Enclosed Loop
2018-08-07 brd 3
2018-08-07 Solid Works Model
2018-08-12 FPGA Main Board
2018-08-12 4427
2018-08-12 Mimas Added
2018-08-16 Components
2018-08-24 Test - Motor
2018-08-24 Motor Driver DB
2018-08-24 FPGA Labelling
2018-08-26 motor driver add
2018-08-26 encoders
2018-08-26 Board file layout
2018-08-28 Tst Board Comp
2018-09-01 ZIP - 6.4
2018-10-04 Added Kicker2018 brd and sch files
2018-11-05 DXF Kicker
2018-11-10 New Main CKt
2018-11-15 Update main board
2018-11-15 New Dimensions for Main CKT
2018-11-22 Placements
2018-11-28 Sch Comp
2018-11-28 Route Complete
2018-12-01 Main Board Clean Up
2018-12-04 Kicker Final
2018-12-15 Error Correction
2018-12-22 main board
2018-12-24 Dimension Correction
2018-12-25 ESP Update
2018-12-26 Current Sensing
2019-01-13 eagle 7 compatible
2019-01-31 Update Kicker
